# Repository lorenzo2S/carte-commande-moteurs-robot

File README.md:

# Carte de commande de deux moteurs – robot (SAÉ BUT GEII)

Carte électronique conçue sous **KiCad** pour piloter les deux moteurs à courant continu d'un robot à deux roues : avancer, reculer et tourner.

Projet réalisé en **2e année de BUT GEII** (parcours Électronique et systèmes embarqués) à l'**IUT de Troyes**, dans le cadre d'une SAÉ. Nous étions un groupe de trois et chacun avait une carte à réaliser : **je me suis occupé de cette carte**, du schéma jusqu'à son intégration dans le robot.

## Ce que j'ai fait

- **Schéma électrique** sous KiCad (Eeschema)
- **Placement et routage** du circuit imprimé **2 couches** (Top / Bottom)
- **Soudure** des composants, dont les deux circuits en boîtier CMS SOIC-16
- **Intégration** de la carte sur le robot et **tests** avec la carte principale (Arduino Nano)

## Fonctionnement

| Élément | Rôle |
|---|---|
| **U1, U2 – VNH7070BAS** (STMicroelectronics) | Ponts en H intégrés à MOSFET, un par moteur (droite / gauche) |
| **J7** – connecteur 7 broches | Liaison avec l'Arduino : signaux `IN_A`, `IN_B` (sens de rotation) et `PWM` (vitesse) pour chaque moteur, + masse |
| **J2, J6** – connecteurs 6 broches | Sorties vers le moteur droit et le moteur gauche |
| **H3, H4** | Entrée d'alimentation **+12 V** / GND (servent aussi de trous de fixation) |

- Le **sens** de chaque moteur est choisi par les entrées `IN_A` / `IN_B` du pont en H.
- La **vitesse** est réglée par un signal **PWM** (MLI) envoyé par l'Arduino.

## Caractéristiques du circuit imprimé

- 2 couches de cuivre, dimensions **49,5 × 33 mm**
- Pistes de **0,6 mm** pour les signaux de commande et de **1,2 mm** pour la puissance (alimentation et sorties moteurs)
- **Plan de masse** (GND) sur toute la surface libre de la carte
- Composants CMS (SOIC-16) et traversants

## Photos

| Carte nue (dessus) | Carte nue (dessous) | Carte montée sur le robot |
|---|---|---|
|  |  |  |

## Contenu du dépôt

```
kicad/   fichiers source KiCad (projet, schéma, circuit imprimé)
docs/    schéma et circuit imprimé en PDF, rendus 3D, liste des composants
photos/  photos de la carte réalisée et du robot
```

- [Schéma électrique (PDF)](docs/schema.pdf)
- [Circuit imprimé – couches Top et Bottom (PDF)](docs/circuit_imprime.pdf)
- [Liste des composants (CSV)](docs/bom.csv)

Les fichiers s'ouvrent avec **KiCad 10**.

## Voir aussi

- [Multimètre numérique à Arduino Nano (SAÉ BUT 1)](https://github.com/lorenzo2S/multimetre-arduino-nano)

## Auteur

**Lorenzo Dos Santos** – étudiant en BUT GEII, parcours ESE, IUT de Troyes

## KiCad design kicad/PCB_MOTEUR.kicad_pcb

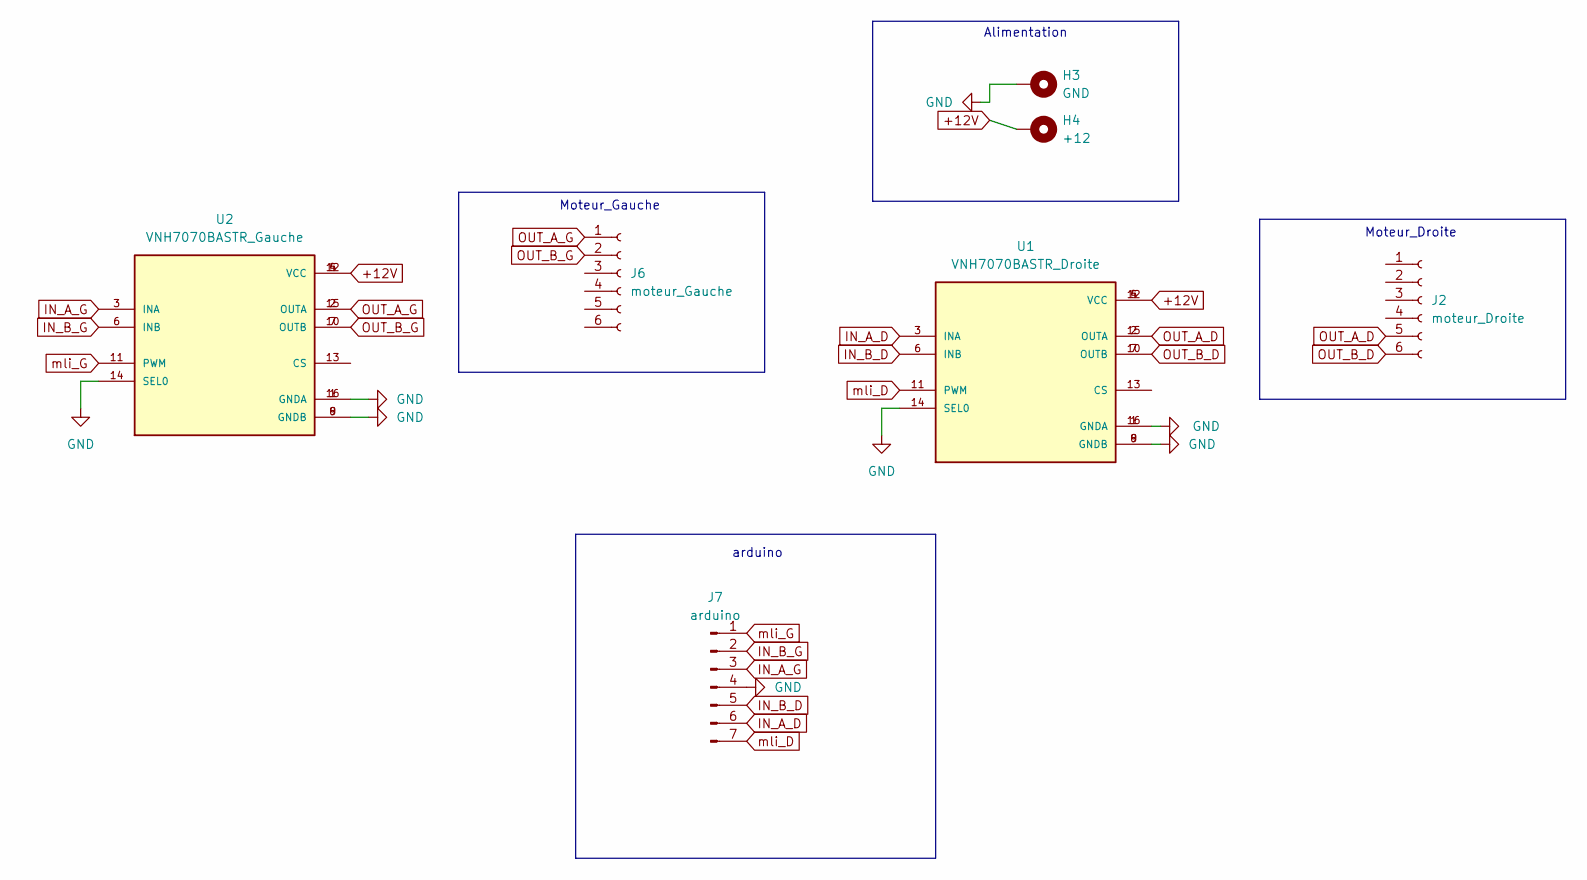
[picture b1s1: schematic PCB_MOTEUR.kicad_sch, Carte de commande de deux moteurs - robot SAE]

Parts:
H3: GND; MountingHole_2.2mm_M2_Pad
H4: +12; MountingHole_2.2mm_M2_Pad
J2: moteur_Droite; PinSocket_1x06_P2.54mm_Vertical
J6: moteur_Gauche; PinSocket_1x06_P2.54mm_Vertical
J7: arduino; PinHeader_1x07_P2.54mm_Horizontal
U1: VNH7070BASTR_Droite; SOIC127P600X175-16N; PARTREV 2
U2: VNH7070BASTR_Gauche; SOIC127P600X175-16N; PARTREV 2

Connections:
+12V: H4.1 (1_1), U1.4 (VCC), U1.5 (VCC), U1.12 (VCC), U2.4 (VCC), U2.5 (VCC), U2.12 (VCC)
GND: H3.1 (1_1), J7.4, U1.1 (GNDA), U1.8 (GNDB), U1.9 (GNDB), U1.14 (SEL0), U1.16 (GNDA), U2.1 (GNDA), U2.8 (GNDB), U2.9 (GNDB), U2.14 (SEL0), U2.16 (GNDA)
IN_A_D: J7.6, U1.3 (INA)
IN_A_G: J7.3, U2.3 (INA)
IN_B_D: J7.5, U1.6 (INB)
IN_B_G: J7.2, U2.6 (INB)
OUT_A_D: J2.5, U1.2 (OUTA), U1.15 (OUTA)
OUT_A_G: J6.1, U2.2 (OUTA), U2.15 (OUTA)
OUT_B_D: J2.6, U1.7 (OUTB), U1.10 (OUTB)
OUT_B_G: J6.2, U2.7 (OUTB), U2.10 (OUTB)
mli_D: J7.7, U1.11 (PWM)
mli_G: J7.1, U2.11 (PWM)

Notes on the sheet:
Alimentation
Moteur_Droite
arduino
Moteur_Gauche

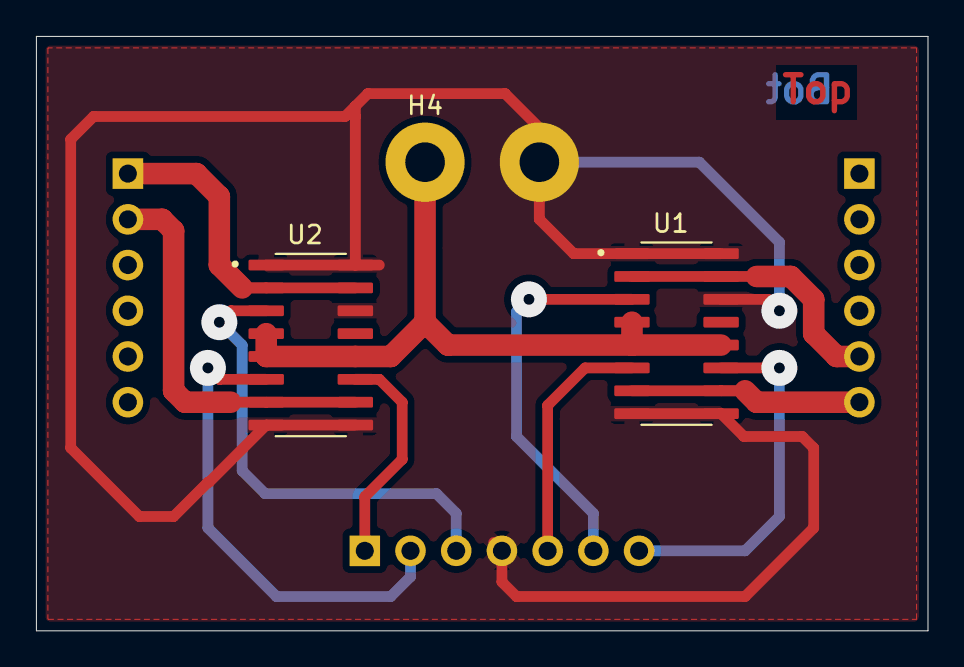
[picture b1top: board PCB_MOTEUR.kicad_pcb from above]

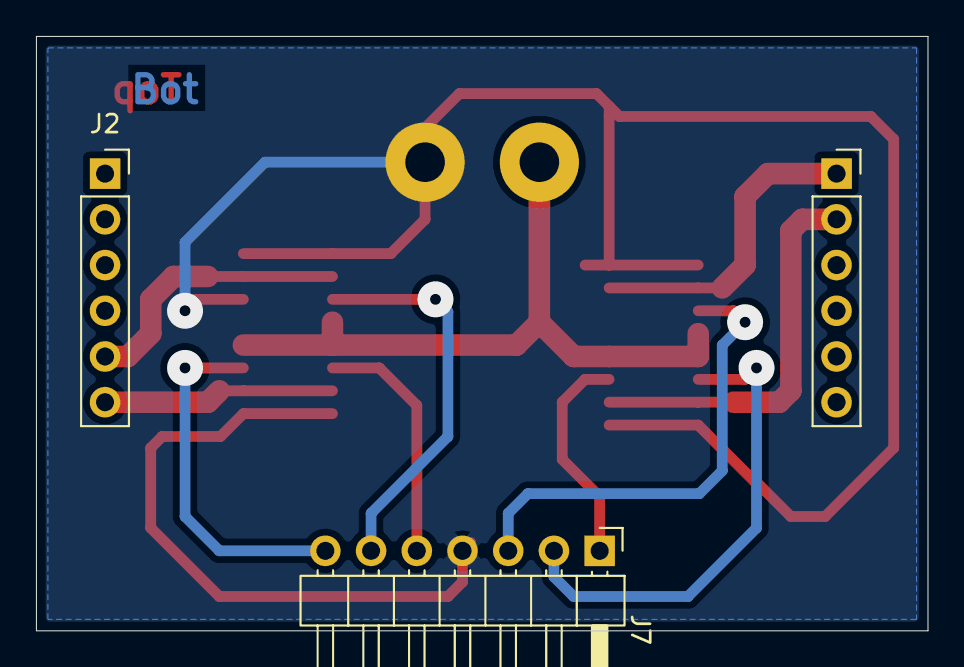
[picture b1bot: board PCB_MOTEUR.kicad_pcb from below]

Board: 2 copper layers, 49.5 x 33.0 mm, 7 parts (3 on the bottom side), 12 nets.

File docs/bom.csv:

"Refs","Value","Footprint","Qty","DNP"
"J2","moteur_Droite","Connector_PinSocket_2.54mm:PinSocket_1x06_P2.54mm_Vertical","1",""
"J6","moteur_Gauche","Connector_PinSocket_2.54mm:PinSocket_1x06_P2.54mm_Vertical","1",""
"J7","arduino","Connector_PinHeader_2.54mm:PinHeader_1x07_P2.54mm_Horizontal","1",""
"U1","VNH7070BASTR_Droite","VNH7070BASTR:SOIC127P600X175-16N","1",""
"U2","VNH7070BASTR_Gauche","VNH7070BASTR:SOIC127P600X175-16N","1",""
